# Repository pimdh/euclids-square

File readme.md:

# Euclid's Square

**THIS IS A WORK IN PROGRESS**

A drum sequencer and sampler based on layering multiple Euclidean rythms. Both firmware and PCB design files are open source licensed under the Creative Commons Attribution 4.0 International License.

## Hardware
It runs on a STM32F722 microcontroller on a custom PCB board.

## Software
The drum machine in written in embedded bare-metal Rust, based on the RTIC framework.

## Samples
Currently, the sampler using the following samples, all in the public domain:
- Hihat https://freesound.org/people/TheFlakesMaster/sounds/399897/
- Snare https://freesound.org/people/alexthegr81/sounds/212208/
- Kick https://freesound.org/people/Mattc90/sounds/351917/

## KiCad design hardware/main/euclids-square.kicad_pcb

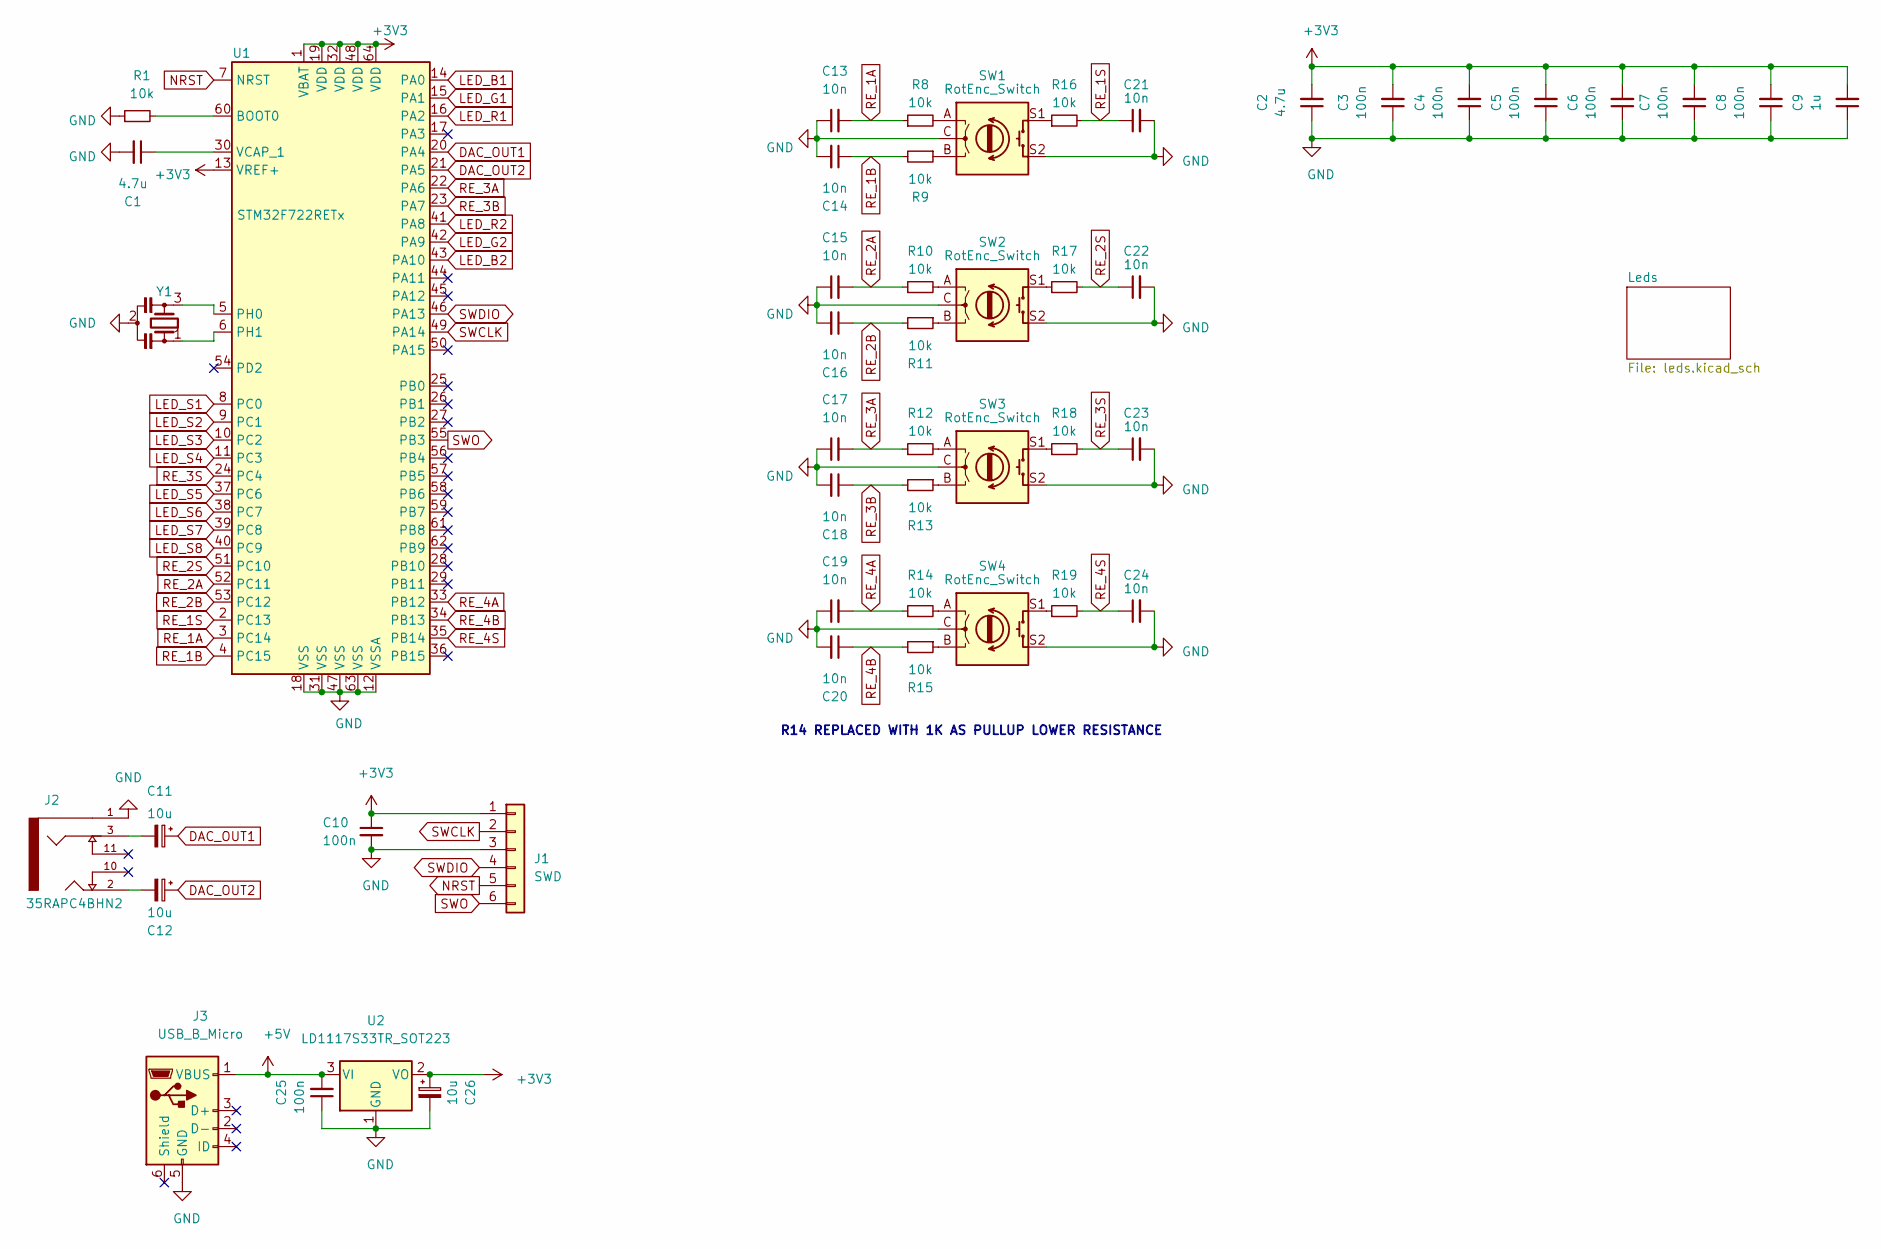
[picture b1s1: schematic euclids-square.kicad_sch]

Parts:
C1, C2: 4.7u; C_0603_1608Metric; Farnell 3013399
C3, C4, C5, C6, C7, C8, C10, C25: 100n; C_0603_1608Metric; Farnell 2581045
C9: 1u; C_0603_1608Metric; Farnell 3013384
C11, C12, C26: 10u; CP_Elec_4x5.4; Farnell 2611355
C13, C14, C15, C16, C17, C18, C19, C20, C21, C22, C23, C24: 10n; C_0603_1608Metric; Farnell 2496828
J1: SWD; PinHeader_1x06_P2.54mm_Vertical
J2: 35RAPC4BHN2; SWITCHCRAFT_35RAPC4BHN2
J3: USB_B_Micro; USB_Micro-B_Amphenol_10118194_Horizontal
R1, R8, R9, R10, R11, R12, R13, R14, R15, R16, R17, R18, R19: 10k; R_0603_1608Metric; Farnell 2670595
SW1, SW2, SW3, SW4: RotEnc_Switch; RotaryEncoder_Alps_EC12E-Switch_Vertical_H20mm; Farnell 2663527
U1: STM32F722RETx; LQFP-64_10x10mm_P0.5mm; Farnell 3365373
U2: LD1117S33TR_SOT223; SOT-223-3_TabPin2; Farnell 1202826
Y1: Resonator_Small; Resonator_SMD-3Pin_3.2x1.3mm; Farnell 3501598

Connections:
+3V3: C2.2, C3.2, C4.2, C5.2, C6.2, C7.2, C8.2, C9.2, C10.1, C26.1, J1.1, U1.1 (VBAT), U1.13 (VREF+), U1.19 (VDD), U1.32 (VDD), U1.48 (VDD), U1.64 (VDD), U2.2 (VO)
+5V: C25.2, J3.1 (VBUS), U2.3 (VI)
DAC_OUT1: C11.1, U1.20 (PA4)
DAC_OUT2: C12.1, U1.21 (PA5)
GND: C1.2, C2.1, C3.1, C4.1, C5.1, C6.1, C7.1, C8.1, C9.1, C10.2, C13.1, C14.2, C15.1, C16.2, C17.1, C18.2, C19.1, C20.2, C21.2, C22.2, C23.2, C24.2, C25.1, C26.2, J1.3, J2.1, J3.5 (GND), R1.1, SW1.C, SW1.S2, SW2.C, SW2.S2, SW3.C, SW3.S2, SW4.C, SW4.S2, U1.12 (VSSA), U1.18 (VSS), U1.31 (VSS), U1.47 (VSS), U1.63 (VSS), U2.1 (GND), Y1.2; also elsewhere on the board
LED_B1: U1.14 (PA0); also elsewhere on the board
LED_B2: U1.43 (PA10); also elsewhere on the board
LED_G1: U1.15 (PA1); also elsewhere on the board
LED_G2: U1.42 (PA9); also elsewhere on the board
LED_R1: U1.16 (PA2); also elsewhere on the board
LED_R2: U1.41 (PA8); also elsewhere on the board
LED_S1: U1.8 (PC0); also elsewhere on the board
LED_S2: U1.9 (PC1); also elsewhere on the board
LED_S3: U1.10 (PC2); also elsewhere on the board
LED_S4: U1.11 (PC3); also elsewhere on the board
LED_S5: U1.37 (PC6); also elsewhere on the board
LED_S6: U1.38 (PC7); also elsewhere on the board
LED_S7: U1.39 (PC8); also elsewhere on the board
LED_S8: U1.40 (PC9); also elsewhere on the board
NRST: J1.5, U1.7 (NRST)
unnamed: C1.1, U1.30 (VCAP_1)
unnamed: C11.2, J2.3
unnamed: C12.2, J2.2
unnamed: R1.2, U1.60 (BOOT0)
unnamed: R8.2, SW1.A
unnamed: R9.1, SW1.B
unnamed: R10.2, SW2.A
unnamed: R11.1, SW2.B
unnamed: R12.2, SW3.A
unnamed: R13.1, SW3.B
unnamed: R14.2, SW4.A
unnamed: R15.1, SW4.B
unnamed: R16.1, SW1.S1
unnamed: R17.1, SW2.S1
unnamed: R18.1, SW3.S1
unnamed: R19.1, SW4.S1
unnamed: U1.5 (PH0), Y1.3
unnamed: U1.6 (PH1), Y1.1
RE_1A: C13.2, R8.1, U1.3 (PC14)
RE_1B: C14.1, R9.2, U1.4 (PC15)
RE_1S: C21.1, R16.2, U1.2 (PC13)
RE_2A: C15.2, R10.1, U1.52 (PC11)
RE_2B: C16.1, R11.2, U1.53 (PC12)
RE_2S: C22.1, R17.2, U1.51 (PC10)
RE_3A: C17.2, R12.1, U1.22 (PA6)
RE_3B: C18.1, R13.2, U1.23 (PA7)
RE_3S: C23.1, R18.2, U1.24 (PC4)
RE_4A: C19.2, R14.1, U1.33 (PB12)
RE_4B: C20.1, R15.2, U1.34 (PB13)
RE_4S: C24.1, R19.2, U1.35 (PB14)
SWCLK: J1.2, U1.49 (PA14)
SWDIO: J1.4, U1.46 (PA13)
SWO: J1.6, U1.55 (PB3)
no_connect_68: J2.10
no_connect_69: J2.11
no_connect_70: J3.2 (D-)
no_connect_71: J3.3 (D+)
no_connect_72: J3.4 (ID)
no_connect_73: J3.6 (Shield)
no_connect_74: U1.17 (PA3)
no_connect_75: U1.25 (PB0)
no_connect_76: U1.26 (PB1)
no_connect_77: U1.27 (PB2)
no_connect_78: U1.28 (PB10)
no_connect_79: U1.29 (PB11)
no_connect_80: U1.36 (PB15)
no_connect_81: U1.44 (PA11)
no_connect_82: U1.45 (PA12)
no_connect_83: U1.50 (PA15)
no_connect_84: U1.54 (PD2)
no_connect_85: U1.56 (PB4)
no_connect_86: U1.57 (PB5)
no_connect_87: U1.58 (PB6)
no_connect_88: U1.59 (PB7)
no_connect_89: U1.61 (PB8)
no_connect_90: U1.62 (PB9)

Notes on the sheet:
R14 REPLACED WITH 1K AS PULLUP LOWER RESISTANCE

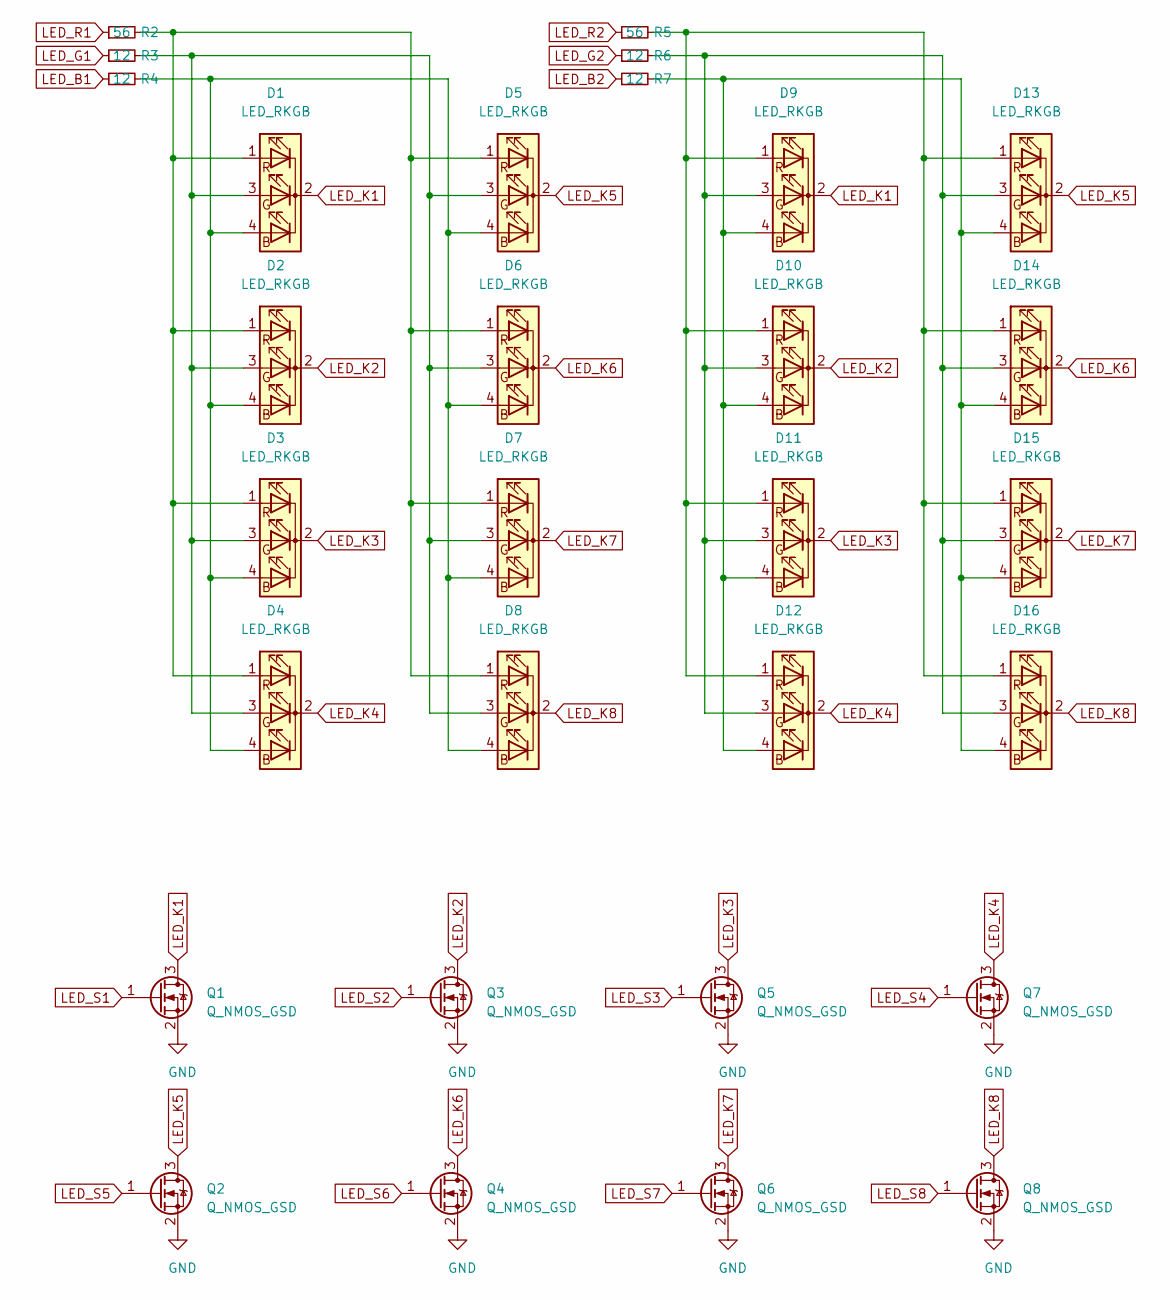
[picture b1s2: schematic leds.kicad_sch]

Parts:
D1, D2, D3, D4, D5, D6, D7, D8, D9, D10, D11, D12, D13, D14, D15, D16: LED_RKGB; LED_D5.0mm-4_RGB
Q1, Q2, Q3, Q4, Q5, Q6, Q7, Q8: Q_NMOS_GSD; SOT-323_SC-70_Handsoldering; Farnell 3619748
R2, R5: 56; R_0603_1608Metric; Farnell 3540045
R3, R4, R6, R7: 12; R_0603_1608Metric; Farnell 2670626

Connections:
GND: Q1.2 (S), Q2.2 (S), Q3.2 (S), Q4.2 (S), Q5.2 (S), Q6.2 (S), Q7.2 (S), Q8.2 (S); also elsewhere on the board
LED_B1: R4.1; also elsewhere on the board
LED_B2: R7.1; also elsewhere on the board
LED_G1: R3.1; also elsewhere on the board
LED_G2: R6.1; also elsewhere on the board
LED_K1: D1.2 (K), D9.2 (K), Q1.3 (D)
LED_K2: D2.2 (K), D10.2 (K), Q3.3 (D)
LED_K3: D3.2 (K), D11.2 (K), Q5.3 (D)
LED_K4: D4.2 (K), D12.2 (K), Q7.3 (D)
LED_K5: D5.2 (K), D13.2 (K), Q2.3 (D)
LED_K6: D6.2 (K), D14.2 (K), Q4.3 (D)
LED_K7: D7.2 (K), D15.2 (K), Q6.3 (D)
LED_K8: D8.2 (K), D16.2 (K), Q8.3 (D)
LED_R1: R2.1; also elsewhere on the board
LED_R2: R5.1; also elsewhere on the board
LED_S1: Q1.1 (G); also elsewhere on the board
LED_S2: Q3.1 (G); also elsewhere on the board
LED_S3: Q5.1 (G); also elsewhere on the board
LED_S4: Q7.1 (G); also elsewhere on the board
LED_S5: Q2.1 (G); also elsewhere on the board
LED_S6: Q4.1 (G); also elsewhere on the board
LED_S7: Q6.1 (G); also elsewhere on the board
LED_S8: Q8.1 (G); also elsewhere on the board
unnamed: D1.1 (RA), D2.1 (RA), D3.1 (RA), D4.1 (RA), D5.1 (RA), D6.1 (RA), D7.1 (RA), D8.1 (RA), R2.2
unnamed: D1.3 (GA), D2.3 (GA), D3.3 (GA), D4.3 (GA), D5.3 (GA), D6.3 (GA), D7.3 (GA), D8.3 (GA), R3.2
unnamed: D1.4 (BA), D2.4 (BA), D3.4 (BA), D4.4 (BA), D5.4 (BA), D6.4 (BA), D7.4 (BA), D8.4 (BA), R4.2
unnamed: D9.1 (RA), D10.1 (RA), D11.1 (RA), D12.1 (RA), D13.1 (RA), D14.1 (RA), D15.1 (RA), D16.1 (RA), R5.2
unnamed: D9.3 (GA), D10.3 (GA), D11.3 (GA), D12.3 (GA), D13.3 (GA), D14.3 (GA), D15.3 (GA), D16.3 (GA), R6.2
unnamed: D9.4 (BA), D10.4 (BA), D11.4 (BA), D12.4 (BA), D13.4 (BA), D14.4 (BA), D15.4 (BA), D16.4 (BA), R7.2

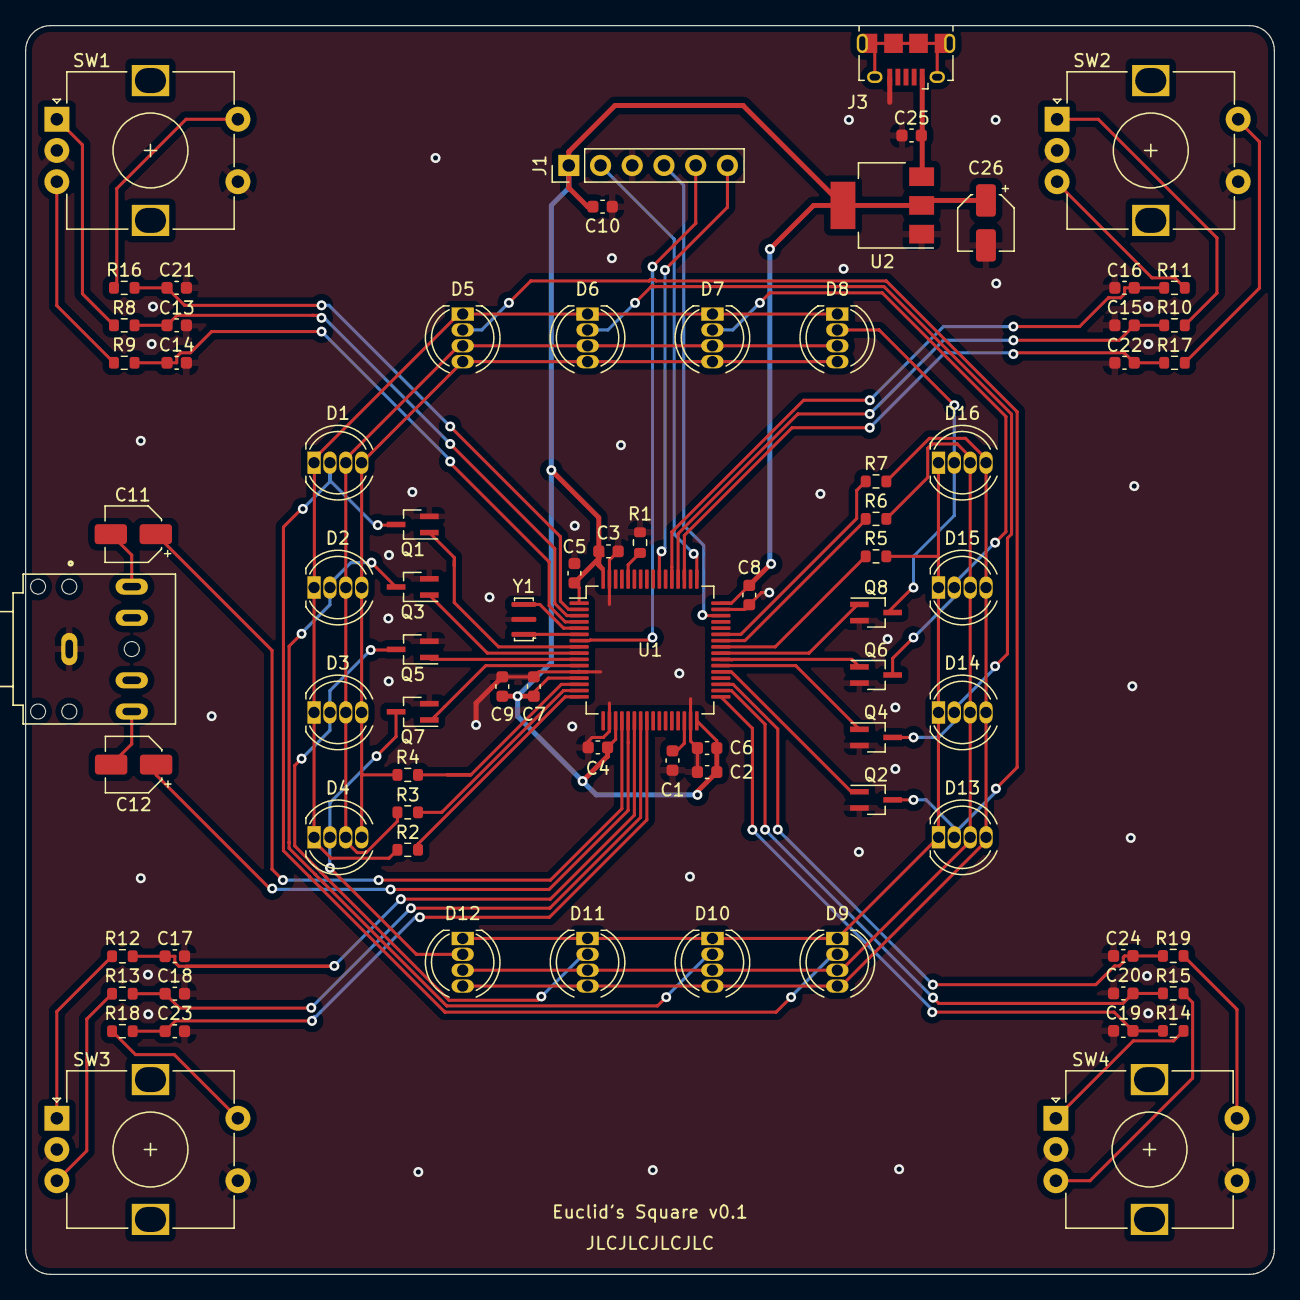
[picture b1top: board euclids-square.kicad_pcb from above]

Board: 2 copper layers, 100.0 x 100.0 mm, 79 parts (0 on the bottom side), 67 nets.

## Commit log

2021-04-22 Added sample attribution
2021-04-22 Partial UI functioning
2021-04-22 Play/pause
2021-04-22 Refactored view, added sequencer view
